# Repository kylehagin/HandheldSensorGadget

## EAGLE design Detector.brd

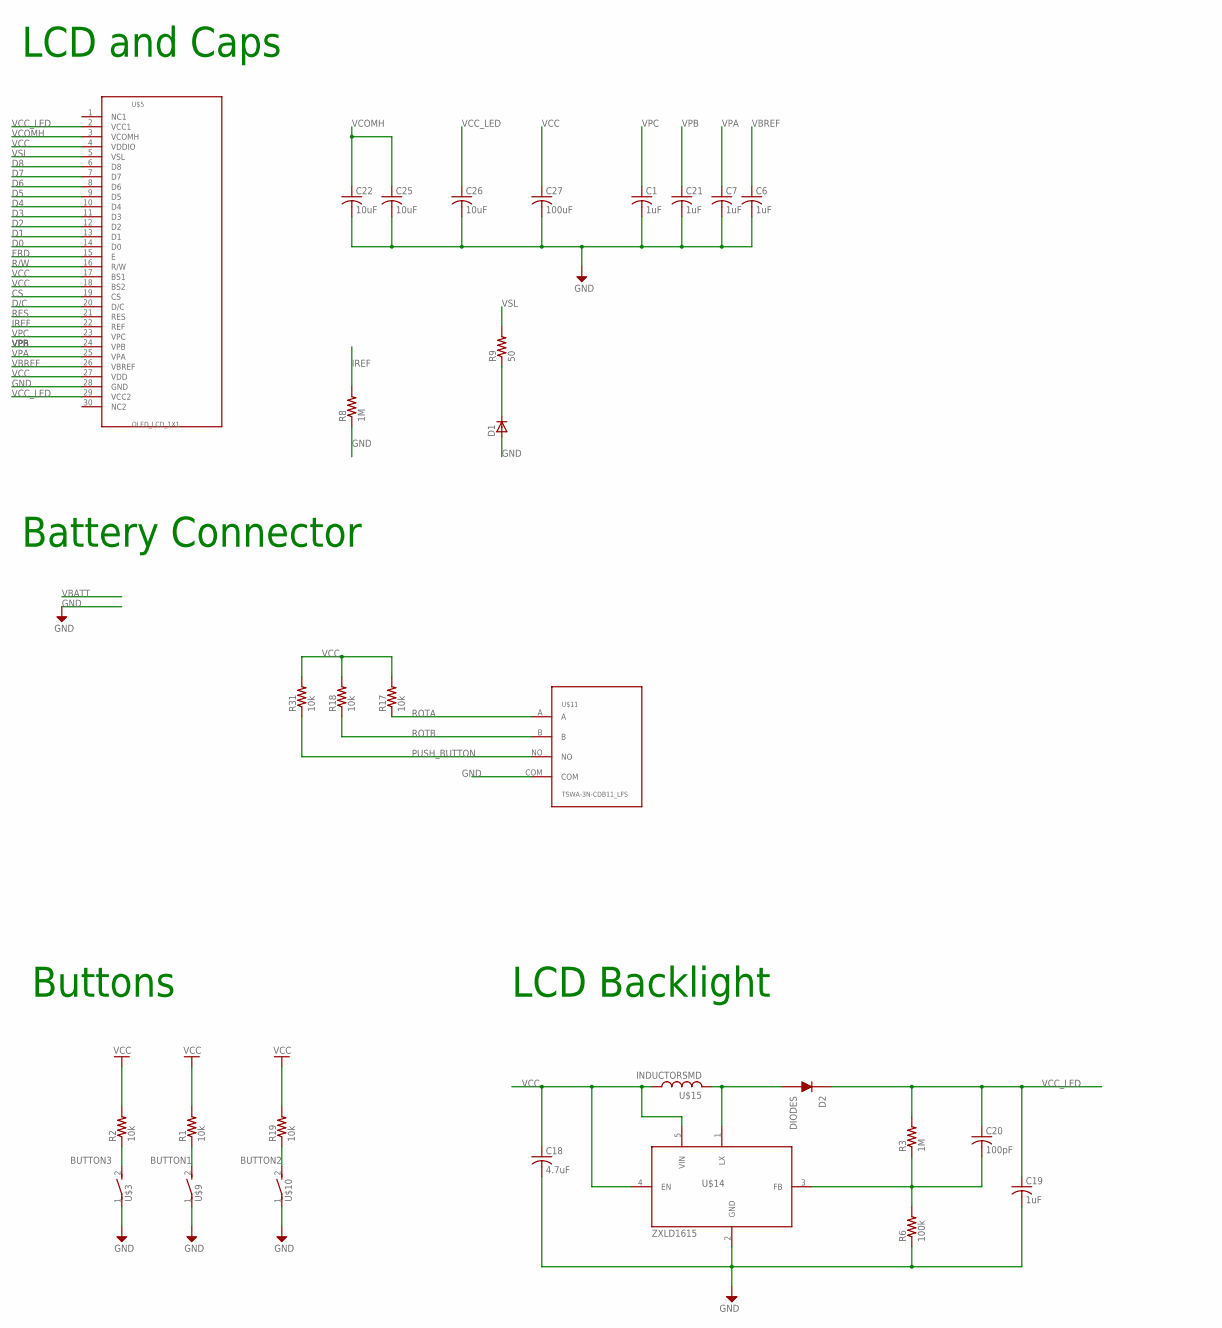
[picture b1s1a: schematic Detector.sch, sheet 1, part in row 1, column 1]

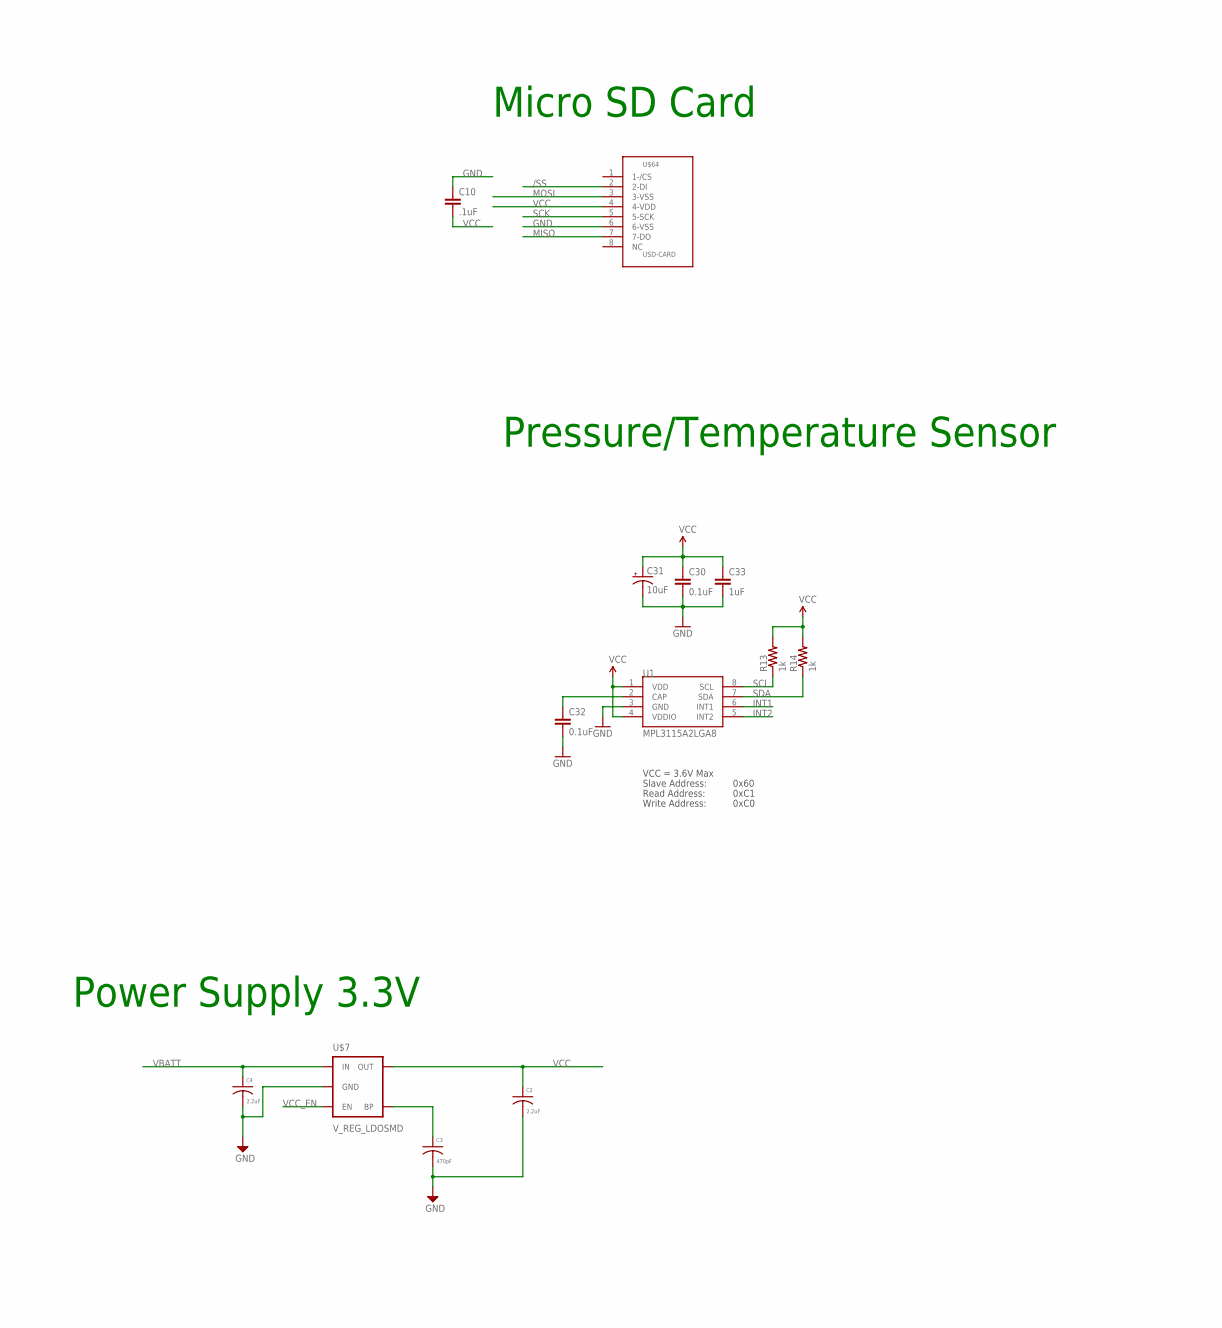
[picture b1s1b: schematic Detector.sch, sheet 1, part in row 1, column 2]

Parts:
C1, C6, C7, C21: 1uF; C0603
C2, C4: 2.2uF; C0603
C3: 470pF; C0603
C10: .1uF; C0402
C18: 4.7uF; C0805K
C19: 1uF; C1206
C20: 100pF; C0402
C22, C25, C26: 10uF; C0603
C27: 100uF; C0603
C30, C32: 0.1uF; 0402-CAP
C31: 10uF; EIA3216
C33: 1uF; 0402-CAP
D1: D-SOD123; SOD123
D2: DIODES; SOD-123
R1, R2, R17, R18, R19, R31: 10k; R0603
R3: 1M; R0805
R6: 100k; R0805
R8: 1M; R0603
R9: 50; R0603
R13, R14: 1k; 0402-RES
U1: MPL3115A2LGA8; LGA8
U$3, U$9, U$10: RGHT-ANGLE-SMT-SWITCH-688-SKRELF; 2.9X3.9X2.0
U$5: OLED_LCD_1X1; 30ZIF
U$7: V_REG_LDOSMD; SOT23-5
U$11: TSWA-3N-CDB11_LFS; TSWA-3N-CB11_LFS
U$14: ZXLD1615; SOT23-5L
U$15: INDUCTORSMD; INDUCTORSMD1
U$64: USD-CARD; 502774-0891

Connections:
/SS: U$64.2 (2-DI); also elsewhere on the board
BUTTON1: R1.1, U$9.2; also elsewhere on the board
BUTTON2: R19.1, U$10.2; also elsewhere on the board
BUTTON3: R2.1, U$3.2; also elsewhere on the board
CS: U$5.19 (CS); also elsewhere on the board
D0: U$5.14 (D0); also elsewhere on the board
D1: U$5.13 (D1); also elsewhere on the board
D2: U$5.12 (D2); also elsewhere on the board
D3: U$5.11 (D3); also elsewhere on the board
D4: U$5.10 (D4); also elsewhere on the board
D5: U$5.9 (D5); also elsewhere on the board
D6: U$5.8 (D6); also elsewhere on the board
D7: U$5.7 (D7); also elsewhere on the board
D8: U$5.6 (D8); also elsewhere on the board
D/C: U$5.20 (D/C); also elsewhere on the board
ERD: U$5.15 (E); also elsewhere on the board
GND: C1.2, C2.2, C3.2, C4.2, C6.2, C7.2, C10.1, C18.2, C19.2, C21.2, C22.2, C25.2, C26.2, C27.2, C30.2, C31.C (-), C32.2, C33.2, D1.2 (A), R6.1, R8.1, U1.3 (GND), U$3.1, U$5.28 (GND), U$7.2 (GND), U$9.1, U$10.1, U$11.COM, U$14.2 (GND), U$64.6 (6-VSS); also elsewhere on the board
INT1: U1.6 (INT1)
INT2: U1.5 (INT2)
IREF: R8.2, U$5.22 (REF)
MISO: U$64.7 (7-DO); also elsewhere on the board
MOSI: U$64.3 (3-VSS); also elsewhere on the board
unnamed: C3.1, U$7.4 (BP)
unnamed: C20.2, R3.1, R6.2, U$14.3 (FB)
unnamed 72: D1.1 (C), R9.1; also elsewhere on the board
unnamed: D2.1 (A1), U$14.1 (LX), U$15.2
unnamed: C32.1, U1.2 (CAP)
PUSH_BUTTON: R31.1, U$11.NO; also elsewhere on the board
R/W: U$5.16 (R/W); also elsewhere on the board
RES: U$5.21 (RES); also elsewhere on the board
ROTA: R17.1, U$11.A; also elsewhere on the board
ROTB: R18.1, U$11.B; also elsewhere on the board
SCK: U$64.5 (5-SCK); also elsewhere on the board
SCL: R13.1, U1.8 (SCL); also elsewhere on the board
SDA: R14.1, U1.7 (SDA); also elsewhere on the board
VBATT: C4.1, U$7.1 (IN); also elsewhere on the board
VBREF: C6.1, U$5.26 (VBREF)
VCC: C2.1, C10.2, C18.1, C27.1, C30.1, C31.A (+), C33.1, R1.2, R2.2, R13.2, R14.2, R17.2, R18.2, R19.2, R31.2, U1.1 (VDD), U1.4 (VDDIO), U$5.4 (VDDIO), U$5.17 (BS1), U$5.18 (BS2), U$5.27 (VDD), U$7.5 (OUT), U$14.4 (EN), U$14.5 (VIN), U$15.1, U$64.4 (4-VDD); also elsewhere on the board
VCC_EN: U$7.3 (EN)
VCC_LED: C19.1, C20.1, C26.1, D2.2 (C), R3.2, U$5.2 (VCC1), U$5.29 (VCC2)
VCOMH: C22.1, C25.1, U$5.3 (VCOMH)
VPA: C7.1, U$5.25 (VPA)
VPB: C21.1, U$5.24 (VPB)
VPC: C1.1, U$5.23 (VPC)
VSL: R9.2, U$5.5 (VSL)

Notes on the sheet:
Battery Connector
Power Supply 3.3V
Buttons
LCD Backlight
LCD and Caps
Micro SD Card
VCC = 3.6V Max
Read Address:
Write Address:
Slave Address:
0x60
0xC1
0xC0
Pressure/Temperature Sensor

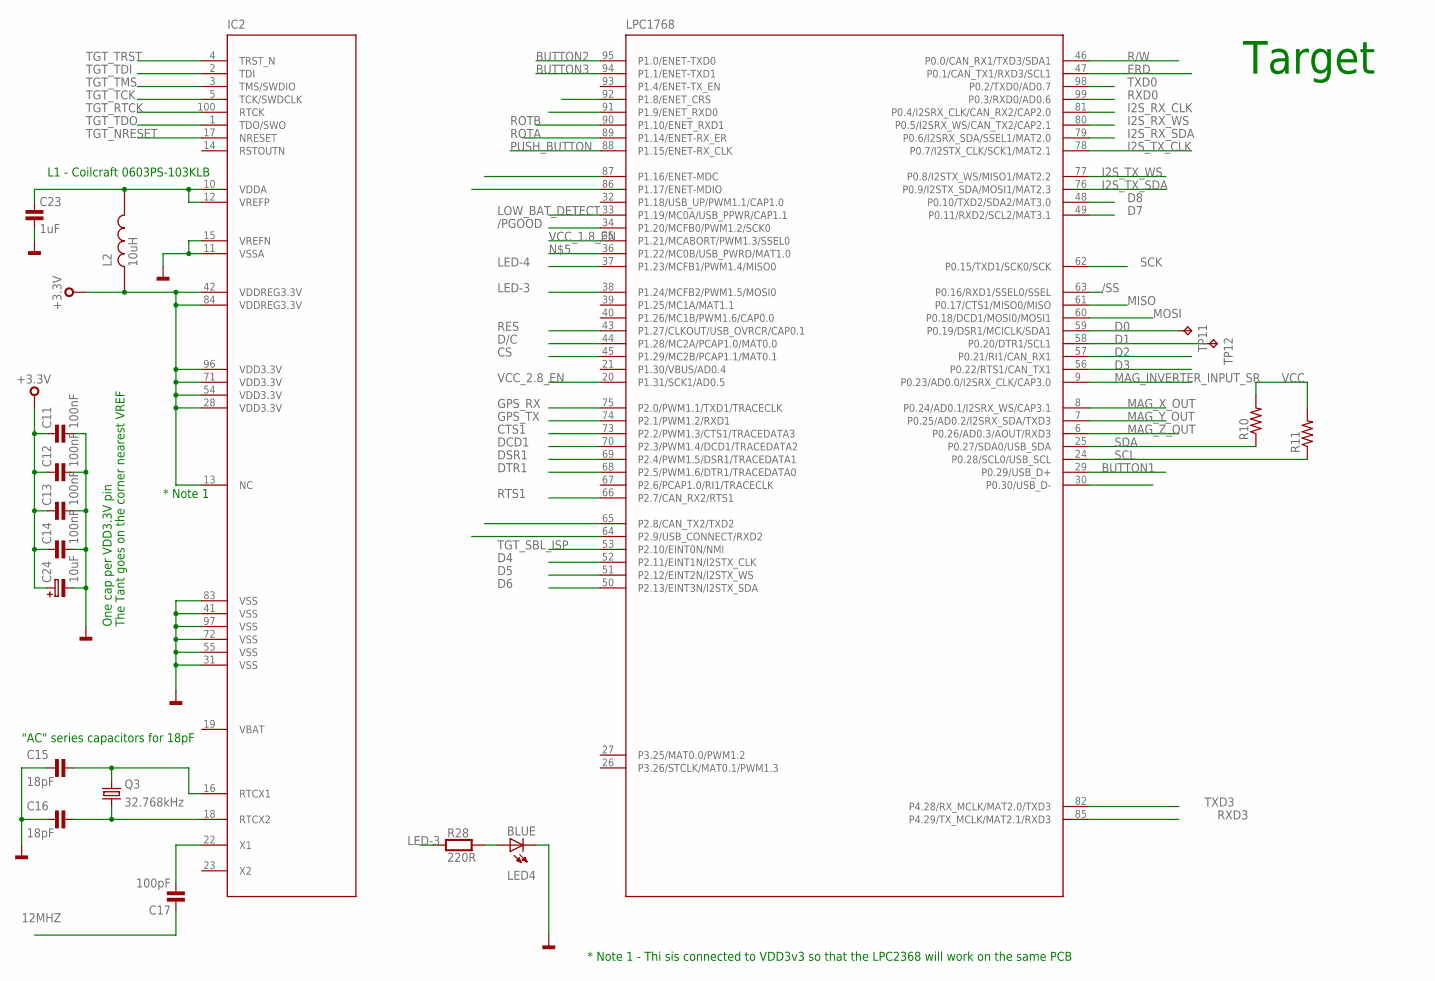
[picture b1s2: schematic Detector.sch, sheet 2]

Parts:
C11, C12, C13, C14: 100nF; 0402
C15, C16: 18pF; 0402
C17: 100pF; 0402
C23: 1uF; 0805
C24: 10uF; C106B
IC2: LPC1768; LQFP100
L2: 10uH; L0603
LED4: BLUE; LED_0805
Q3: 32.768kHz; FC135
R10, R11: R-US_R0402; R0402
R28: 220R; 0402
TP11, TP12: TPTP06R; TP06R

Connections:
12MHZ: C17.1; also elsewhere on the board
/PGOOD: IC2.34 (P1.20/MCFB0/PWM1.2/SCK0)
/SS: IC2.63 (P0.16/RXD1/SSEL0/SSEL); also elsewhere on the board
BUTTON1: IC2.29 (P0.29/USB_D+); also elsewhere on the board
BUTTON2: IC2.95 (P1.0/ENET-TXD0); also elsewhere on the board
BUTTON3: IC2.94 (P1.1/ENET-TXD1); also elsewhere on the board
CS: IC2.45 (P1.29/MC2B/PCAP1.1/MAT0.1); also elsewhere on the board
CTS1: IC2.73 (P2.2/PWM1.3/CTS1/TRACEDATA3)
D0: IC2.59 (P0.19/DSR1/MCICLK/SDA1), TP11.TP; also elsewhere on the board
D1: IC2.58 (P0.20/DTR1/SCL1), TP12.TP; also elsewhere on the board
D2: IC2.57 (P0.21/RI1/CAN_RX1); also elsewhere on the board
D3: IC2.56 (P0.22/RTS1/CAN_TX1); also elsewhere on the board
D4: IC2.52 (P2.11/EINT1N/I2STX_CLK); also elsewhere on the board
D5: IC2.51 (P2.12/EINT2N/I2STX_WS); also elsewhere on the board
D6: IC2.50 (P2.13/EINT3N/I2STX_SDA); also elsewhere on the board
D7: IC2.49 (P0.11/RXD2/SCL2/MAT3.1); also elsewhere on the board
D8: IC2.48 (P0.10/TXD2/SDA2/MAT3.0); also elsewhere on the board
D/C: IC2.44 (P1.28/MC2A/PCAP1.0/MAT0.0); also elsewhere on the board
DCD1: IC2.70 (P2.3/PWM1.4/DCD1/TRACEDATA2)
DSR1: IC2.69 (P2.4/PWM1.5/DSR1/TRACEDATA1)
DTR1: IC2.68 (P2.5/PWM1.6/DTR1/TRACEDATA0)
ERD: IC2.47 (P0.1/CAN_TX1/RXD3/SCL1); also elsewhere on the board
GND: C11.2, C12.2, C13.2, C14.2, C15.1, C16.1, C23.2, C24.2, IC2.11 (VSSA), IC2.15 (VREFN), IC2.31 (VSS), IC2.41 (VSS), IC2.55 (VSS), IC2.72 (VSS), IC2.83 (VSS), IC2.97 (VSS), LED4.K; also elsewhere on the board
GPS_RX: IC2.75 (P2.0/PWM1.1/TXD1/TRACECLK)
GPS_TX: IC2.74 (P2.1/PWM1.2/RXD1)
I2S_RX_CLK: IC2.81 (P0.4/I2SRX_CLK/CAN_RX2/CAP2.0); also elsewhere on the board
I2S_RX_SDA: IC2.79 (P0.6/I2SRX_SDA/SSEL1/MAT2.0); also elsewhere on the board
I2S_RX_WS: IC2.80 (P0.5/I2SRX_WS/CAN_TX2/CAP2.1); also elsewhere on the board
I2S_TX_CLK: IC2.78 (P0.7/I2STX_CLK/SCK1/MAT2.1); also elsewhere on the board
I2S_TX_SDA: IC2.76 (P0.9/I2STX_SDA/MOSI1/MAT2.3); also elsewhere on the board
I2S_TX_WS: IC2.77 (P0.8/I2STX_WS/MISO1/MAT2.2)
IC6_RTC1: C15.2, IC2.16 (RTCX1), Q3.X2 (2)
IC6_RTC2: C16.2, IC2.18 (RTCX2), Q3.X1 (1)
IC6_XTAL1: C17.2, IC2.22 (X1)
LED-3: IC2.38 (P1.24/MCFB2/PWM1.5/MOSI0), R28.1
LED-4: IC2.37 (P1.23/MCFB1/PWM1.4/MISO0)
LOW_BAT_DETECT: IC2.33 (P1.19/MC0A/USB_PPWR/CAP1.1)
MAG_INVERTER_INPUT_SR: IC2.9 (P0.23/AD0.0/I2SRX_CLK/CAP3.0)
MAG_X_OUT: IC2.8 (P0.24/AD0.1/I2SRX_WS/CAP3.1); also elsewhere on the board
MAG_Y_OUT: IC2.7 (P0.25/AD0.2/I2SRX_SDA/TXD3); also elsewhere on the board
MAG_Z_OUT: IC2.6 (P0.26/AD0.3/AOUT/RXD3); also elsewhere on the board
MISO: IC2.61 (P0.17/CTS1/MISO0/MISO); also elsewhere on the board
MOSI: IC2.60 (P0.18/DCD1/MOSI0/MOSI1); also elsewhere on the board
unnamed 72: IC2.36 (P1.22/MC0B/USB_PWRD/MAT1.0); also elsewhere on the board
unnamed: LED4.A, R28.2
unnamed: C23.1, IC2.10 (VDDA), IC2.12 (VREFP), L2.P$2
PUSH_BUTTON: IC2.88 (P1.15/ENET-RX_CLK); also elsewhere on the board
R/W: IC2.46 (P0.0/CAN_RX1/TXD3/SDA1); also elsewhere on the board
RES: IC2.43 (P1.27/CLKOUT/USB_OVRCR/CAP0.1); also elsewhere on the board
ROTA: IC2.89 (P1.14/ENET-RX_ER); also elsewhere on the board
ROTB: IC2.90 (P1.10/ENET_RXD1); also elsewhere on the board
RTS1: IC2.66 (P2.7/CAN_RX2/RTS1)
RXD0: IC2.99 (P0.3/RXD0/AD0.6); also elsewhere on the board
RXD3: IC2.85 (P4.29/TX_MCLK/MAT2.1/RXD3)
SCK: IC2.62 (P0.15/TXD1/SCK0/SCK); also elsewhere on the board
SCL: IC2.24 (P0.28/SCL0/USB_SCL), R11.1; also elsewhere on the board
SDA: IC2.25 (P0.27/SDA0/USB_SDA), R10.1; also elsewhere on the board
TGT_NRESET: IC2.17 (NRESET); also elsewhere on the board
TGT_RTCK: IC2.100 (RTCK)
TGT_SBL_ISP: IC2.53 (P2.10/EINT0N/NMI); also elsewhere on the board
TGT_TCK: IC2.5 (TCK/SWDCLK)
TGT_TDI: IC2.2 (TDI)
TGT_TDO: IC2.1 (TDO/SWO)
TGT_TMS: IC2.3 (TMS/SWDIO)
TGT_TRST: IC2.4 (TRST_N)
TXD0: IC2.98 (P0.2/TXD0/AD0.7); also elsewhere on the board
TXD3: IC2.82 (P4.28/RX_MCLK/MAT2.0/TXD3)
VCC: C11.1, C12.1, C13.1, C14.1, C24.1, IC2.13 (NC), IC2.28 (VDD3.3V), IC2.42 (VDDREG3.3V), IC2.54 (VDD3.3V), IC2.71 (VDD3.3V), IC2.84 (VDDREG3.3V), IC2.96 (VDD3.3V), L2.P$1, R10.2, R11.2; also elsewhere on the board
VCC_1.8_EN: IC2.35 (P1.21/MCABORT/PWM1.3/SSEL0)
VCC_2.8_EN: IC2.20 (P1.31/SCK1/AD0.5)

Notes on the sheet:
The Tant goes on the corner nearest VREF
L1 - Coilcraft 0603PS-103KLB
"AC" series capacitors for 18pF
One cap per VDD3.3V pin
Target
* Note 1
* Note 1 - Thi sis connected to VDD3v3 so that the LPC2368 will work on the same PCB

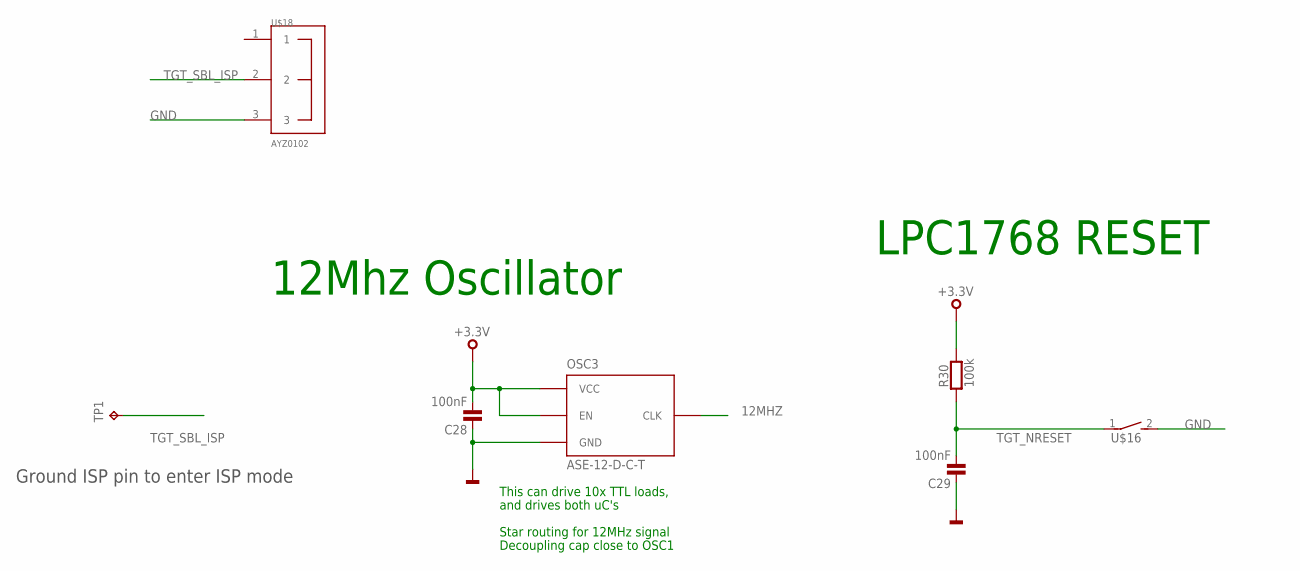
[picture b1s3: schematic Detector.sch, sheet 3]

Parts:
C28, C29: 100nF; 0402
OSC3: ASE-12-D-C-T; OSC3.2X.2.5
R30: 100k; 0402
TP1: TPTP09R; TP09R
U$16: RGHT-ANGLE-SMT-SWITCH-688-SKRELF; 2.9X3.9X2.0
U$18: AYZ0102

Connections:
12MHZ: OSC3.P$3 (CLK); also elsewhere on the board
GND: C28.1, C29.1, OSC3.P$2 (GND), U$16.2, U$18.3; also elsewhere on the board
TGT_NRESET: C29.2, R30.1, U$16.1; also elsewhere on the board
TGT_SBL_ISP: TP1.TP, U$18.2; also elsewhere on the board
VCC: C28.2, OSC3.P$1 (EN), OSC3.P$4 (VCC), R30.2; also elsewhere on the board

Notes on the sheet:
Ground ISP pin to enter ISP mode
This can drive 10x TTL loads,
and drives both uC's
Star routing for 12MHz signal
Decoupling cap close to OSC1
12Mhz Oscillator
LPC1768 RESET

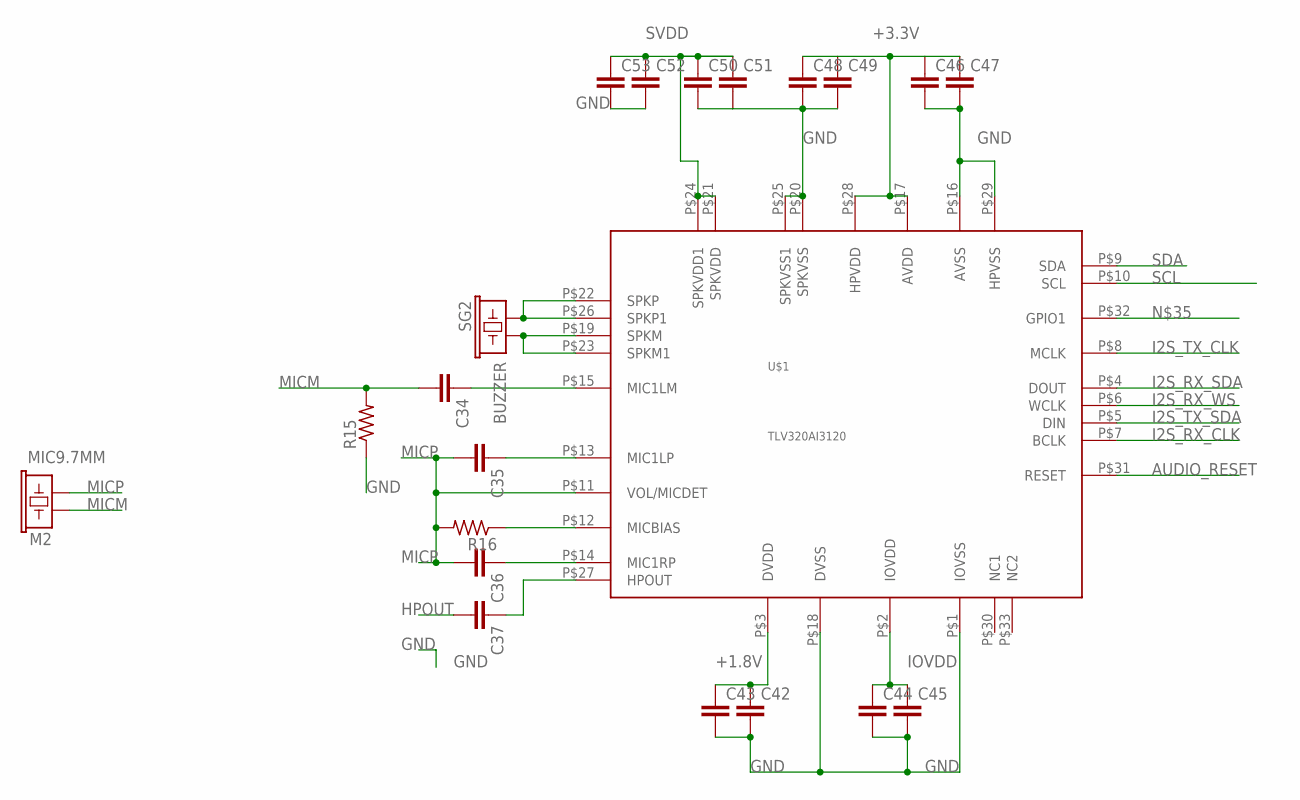
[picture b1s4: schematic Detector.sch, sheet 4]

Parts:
C34, C35, C36, C37, C42, C43, C44, C45, C46, C47, C48, C49, C50, C51, C52, C53: C-EUC0402; C0402
M2: MIC9.7MM; MIC-9.7MM
R15, R16: R-US_R0402; R0402
SG2: BUZZER; SMS-1308
U$1: TLV320AI3120; QFN-32

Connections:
+1.8V: C42.1, C43.1, U$1.P$3 (DVDD)
+3.3V: C46.1, C47.1, C48.1, C49.1, U$1.P$17 (AVDD), U$1.P$28 (HPVDD)
AUDIO_RESET: U$1.P$31 (RESET)
GND: C42.2, C43.2, C44.2, C45.2, C46.2, C47.2, C48.2, C49.2, C50.2, C51.2, C52.2, C53.2, R15.1, U$1.P$1 (IOVSS), U$1.P$16 (AVSS), U$1.P$18 (DVSS), U$1.P$20 (SPKVSS), U$1.P$25 (SPKVSS1), U$1.P$29 (HPVSS); also elsewhere on the board
HPOUT: C37.2
I2S_RX_CLK: U$1.P$7 (BCLK); also elsewhere on the board
I2S_RX_SDA: U$1.P$4 (DOUT); also elsewhere on the board
I2S_RX_WS: U$1.P$6 (WCLK); also elsewhere on the board
I2S_TX_CLK: U$1.P$8 (MCLK); also elsewhere on the board
I2S_TX_SDA: U$1.P$5 (DIN); also elsewhere on the board
IOVDD: C44.1, C45.1, U$1.P$2 (IOVDD)
MICM: C34.2, M2.2, R15.2
MICP: C35.2, C36.2, M2.1, R16.2, U$1.P$11 (VOL/MICDET)
unnamed: SG2.+ (1), U$1.P$22 (SPKP), U$1.P$26 (SPKP1)
unnamed: SG2.- (2), U$1.P$19 (SPKM), U$1.P$23 (SPKM1)
unnamed: C34.1, U$1.P$15 (MIC1LM)
unnamed: R16.1, U$1.P$12 (MICBIAS)
unnamed: C35.1, U$1.P$13 (MIC1LP)
unnamed: C36.1, U$1.P$14 (MIC1RP)
unnamed: C37.1, U$1.P$27 (HPOUT)
SCL: U$1.P$10 (SCL); also elsewhere on the board
SDA: U$1.P$9 (SDA); also elsewhere on the board
SVDD: C50.1, C51.1, C52.1, C53.1, U$1.P$21 (SPKVDD), U$1.P$24 (SPKVDD1)

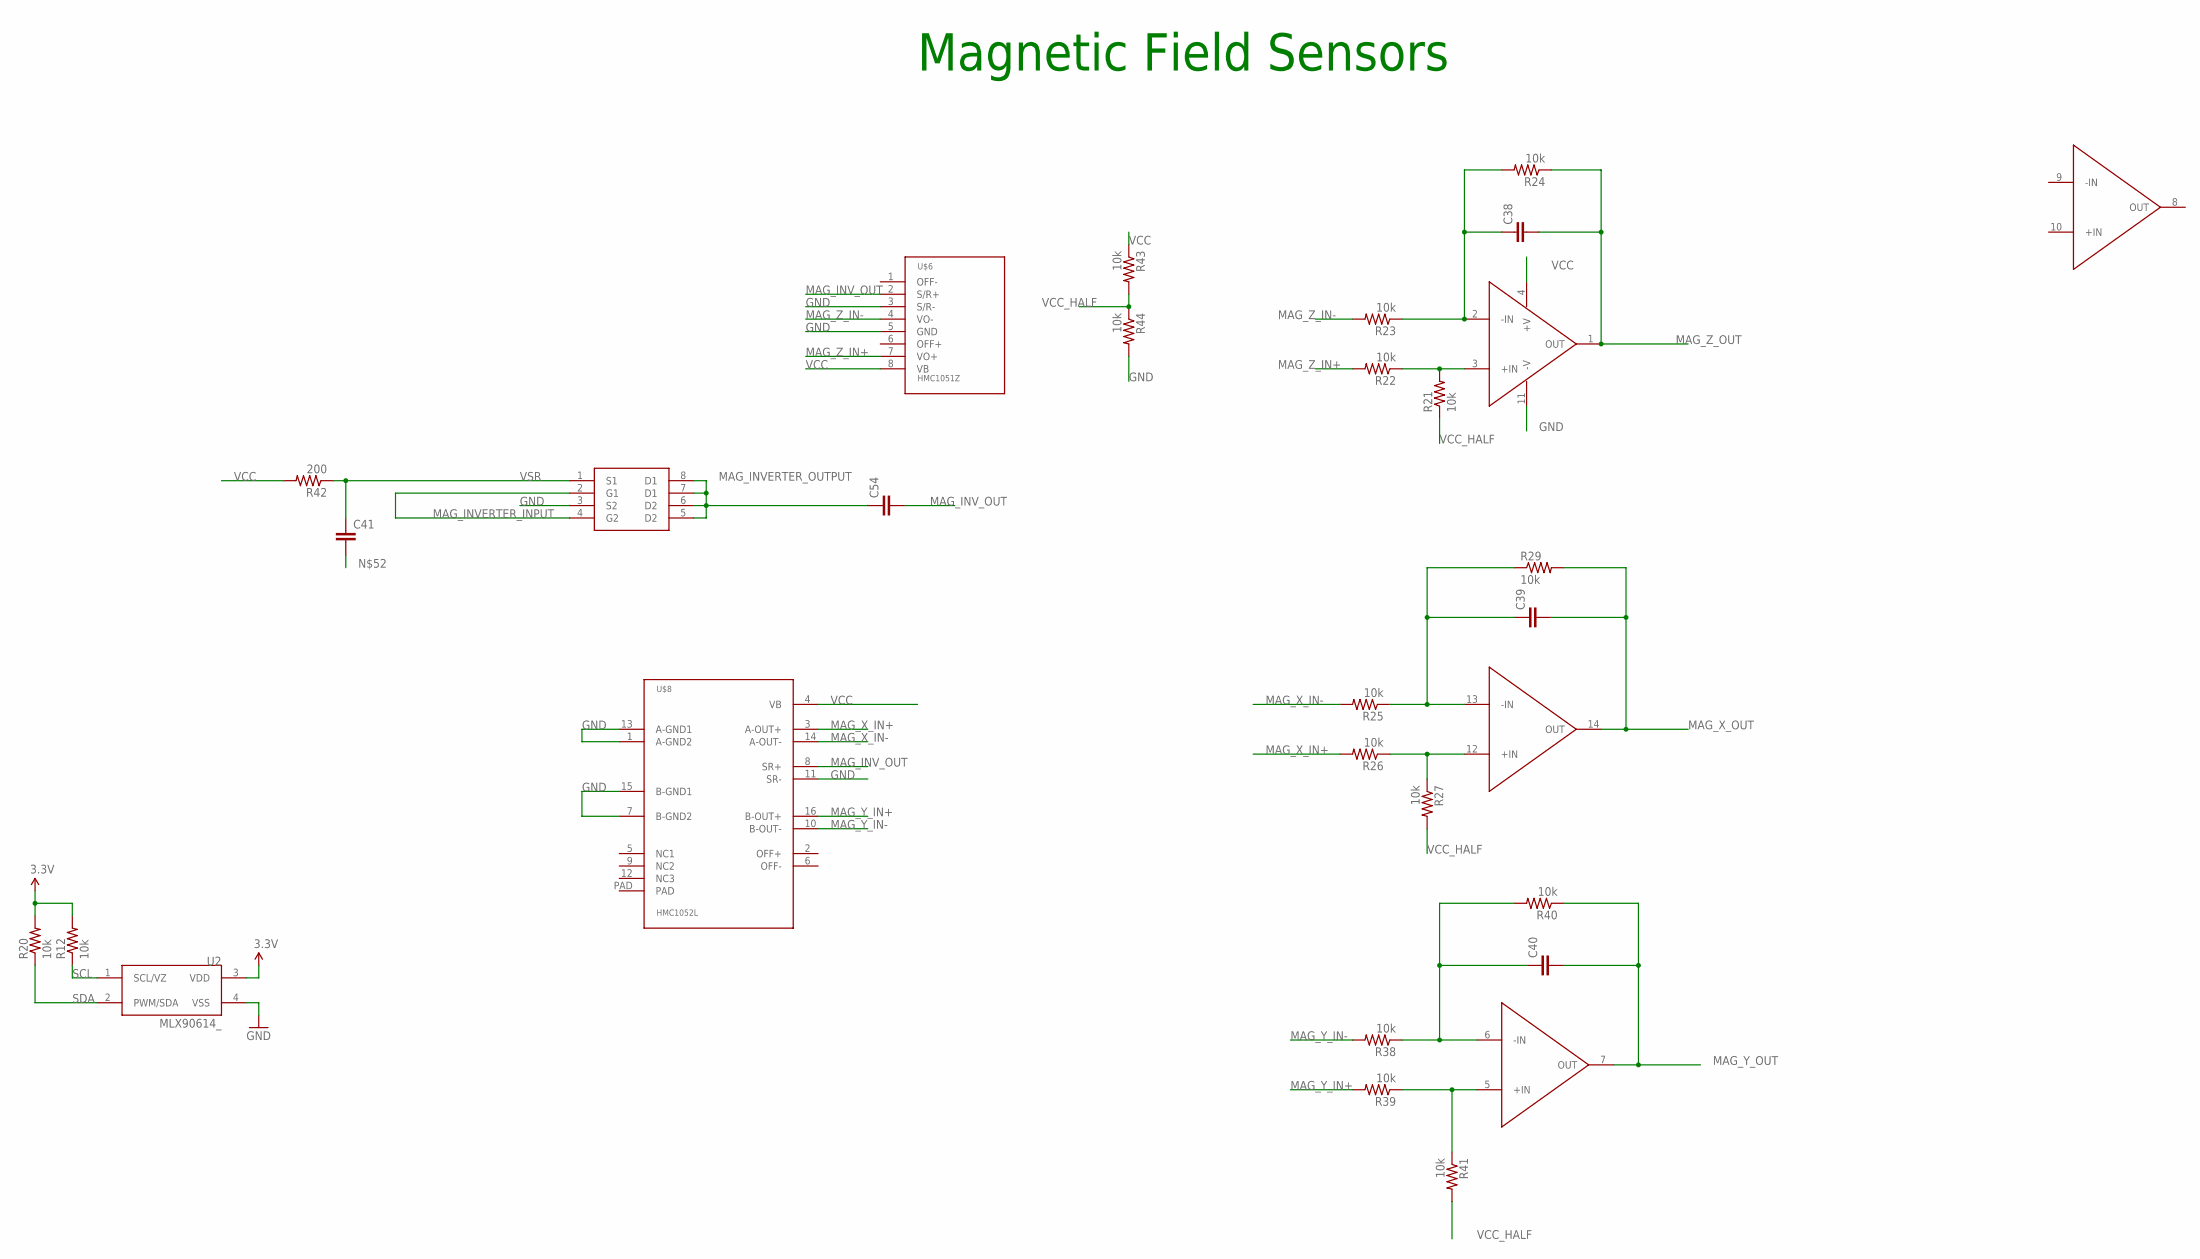
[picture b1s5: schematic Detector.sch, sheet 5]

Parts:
C38, C39, C40, C41, C54: C-EUC0402; C0402
R12, R20, R21, R22, R23, R24, R25, R26, R27, R29, R38, R39, R40, R41, R43, R44: 10k; 0402-RES
R42: 200; 0402-RES
U2: MLX90614_; TO-39
U$6: HMC1051Z; HMC-SIP
U$8: HMC1052L; LCC-16
U$12: LMV324; SO014
U$13: IRF7507; MSOP8

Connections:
3.3V: R12.2, R20.2, U2.3 (VDD)
+IN: U$12.10 (+IN)
-IN: U$12.9 (-IN)
GND: R44.2, U2.4 (VSS), U$6.3 (S/R-), U$6.5 (GND), U$8.1 (A-GND2), U$8.7 (B-GND2), U$8.11 (SR-), U$8.13 (A-GND1), U$8.15 (B-GND1), U$12.11 (-V), U$13.3 (S2); also elsewhere on the board
MAG_INVERTER_INPUT: U$13.2 (G1), U$13.4 (G2)
MAG_INVERTER_OUTPUT: C54.1, U$13.5 (D2), U$13.6 (D2), U$13.7 (D1), U$13.8 (D1)
MAG_INV_OUT: C54.2, U$6.2 (S/R+), U$8.8 (SR+)
MAG_X_IN+: R26.2, U$8.3 (A-OUT+)
MAG_X_IN-: R25.2, U$8.14 (A-OUT-)
MAG_X_OUT: C39.2, R29.2, U$12.14 (OUT); also elsewhere on the board
MAG_Y_IN+: R39.2, U$8.16 (B-OUT+)
MAG_Y_IN-: R38.2, U$8.10 (B-OUT-)
MAG_Y_OUT: C40.2, R40.1, U$12.7 (OUT); also elsewhere on the board
MAG_Z_IN+: R22.2, U$6.7 (VO+)
MAG_Z_IN-: R23.2, U$6.4 (VO-)
MAG_Z_OUT: C38.2, R24.1, U$12.1 (OUT); also elsewhere on the board
unnamed: C38.1, R23.1, R24.2, U$12.2 (-IN)
unnamed: R21.2, R22.1, U$12.3 (+IN)
unnamed: C39.1, R25.1, R29.1, U$12.13 (-IN)
unnamed: R26.1, R27.1, U$12.12 (+IN)
unnamed: C40.1, R38.1, R40.2, U$12.6 (-IN)
unnamed: R39.1, R41.1, U$12.5 (+IN)
OUT: U$12.8 (OUT)
SCL: R12.1, U2.1 (SCL/VZ); also elsewhere on the board
SDA: R20.1, U2.2 (PWM/SDA); also elsewhere on the board
VCC: R42.2, R43.1, U$6.8 (VB), U$8.4 (VB), U$12.4 (+V); also elsewhere on the board
VCC_HALF: R21.1, R27.2, R41.2, R43.2, R44.1
VSR: C41.1, R42.1, U$13.1 (S1)

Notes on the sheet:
Magnetic Field Sensors

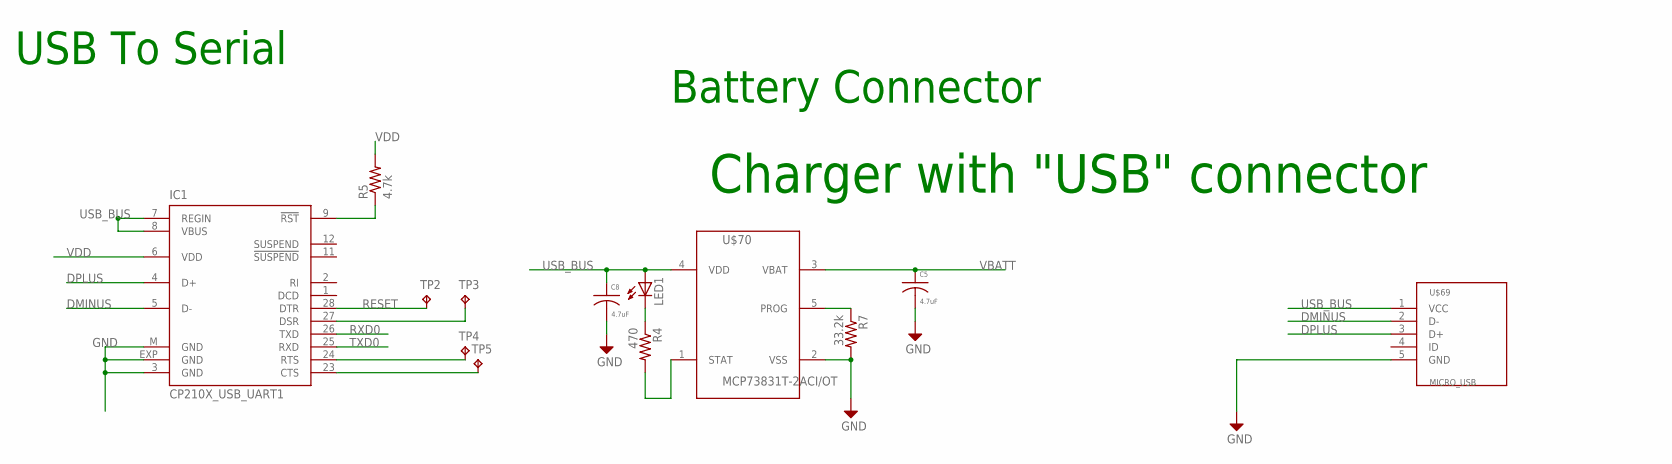
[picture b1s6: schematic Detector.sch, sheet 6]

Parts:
C5, C8: 4.7uF; C0603
IC1: CP210X_USB_UART1; MLP28
LED1: LEDCHIP-LED0603; CHIP-LED0603
R4: 470; R0402
R5: 4.7k; R0402
R7: 33.2k; R0402
TP2, TP3, TP4, TP5: TPTP06R; TP06R
U$69: MICRO_USB
U$70: MCP73831T-2ACI/OT; SOT23-5L

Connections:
CHG_STAT: R4.2, U$70.1 (STAT)
DMINUS: IC1.5 (D-), U$69.2 (D-)
DPLUS: IC1.4 (D+), U$69.3 (D+)
GND: C5.2, C8.2, IC1.3 (GND), IC1.EXP (GND), IC1.M (GND), R7.2, U$69.5 (GND), U$70.2 (VSS); also elsewhere on the board
unnamed: IC1.9 (!RST), R5.1
unnamed: IC1.24 (RTS), TP4.TP
unnamed: IC1.23 (CTS), TP5.TP
unnamed: IC1.27 (DSR), TP3.TP
unnamed: LED1.C, R4.1
unnamed: R7.1, U$70.5 (PROG)
RESET: IC1.28 (DTR), TP2.TP
RXD0: IC1.26 (TXD); also elsewhere on the board
TXD0: IC1.25 (RXD); also elsewhere on the board
USB_BUS: C8.1, IC1.7 (REGIN), IC1.8 (VBUS), LED1.A, U$69.1 (VCC), U$70.4 (VDD)
VBATT: C5.1, U$70.3 (VBAT); also elsewhere on the board
VDD: IC1.6 (VDD), R5.2

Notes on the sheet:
USB To Serial
Battery Connector
Charger with "USB" connector

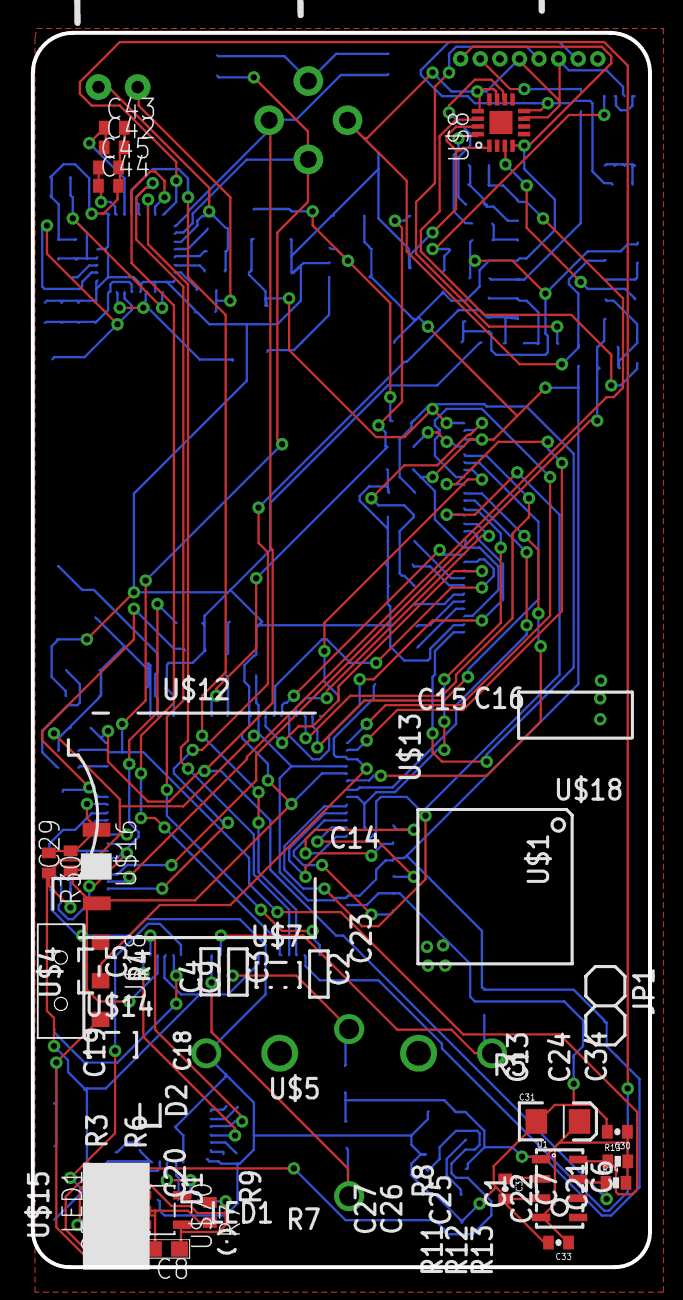
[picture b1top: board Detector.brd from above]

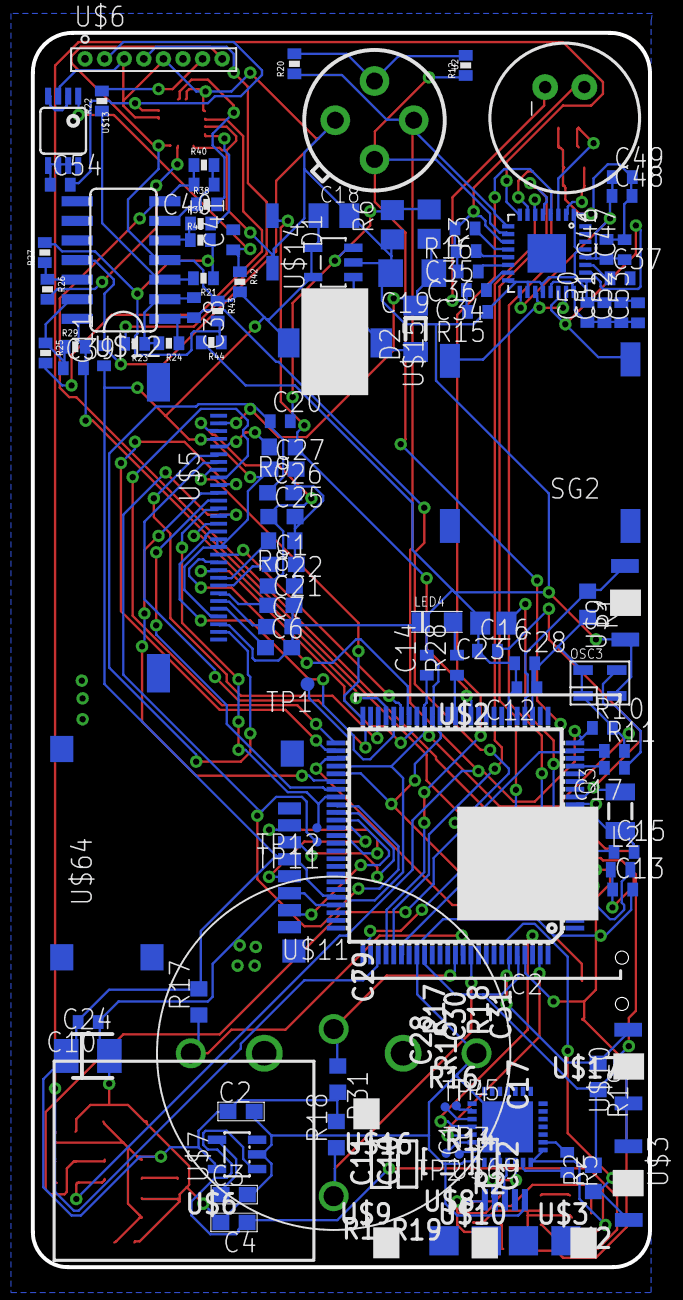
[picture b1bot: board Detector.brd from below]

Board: 2 copper layers, 40.0 x 80.0 mm, 129 parts (107 on the bottom side), 104 nets.

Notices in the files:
parts and their libraries:
SparkFun-Sensors: Licensing: CC v3.0 Share-Alike You are welcome to use this library for commercial purposes.
